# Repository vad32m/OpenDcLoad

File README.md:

#### Configurable parameters

| Configurable parameter | Range        | Granularity | Number of Values |
| ---------------------- | ------------ | ----------- | ---------------- |
| Current (CC mode)      | 0 - 10 A     | 10 mA       | 1000             |
| Voltage (CV mode)      | 1 - 10 V     | 10 mV       | 900              |
|                        | 10 - 100 V   | 100 mV      | 900              |
|                        | 100 - 360 V  | 1 V         | 260              |
| Resistance (CR mode)   | 0.5 - 10 Ohm | 50 mOhm     | 190              |
|                        | 10 - 200 Ohm | 500 mOhm    | 190              |
| Power (CP mode)        | ????         | ????        | ????             |

#### Limits

| Limit type | Applicable mode | Limit value |
| ---------- | --------------- | ----------- |
| Power      | All modes       | 100 W max   |
| Current    | All modes       | 10 A max    |
| Voltage    | All modes       | 1 - 360 V   |
| Resistance | All modes       | 0.5 Ohm min |

#### Measured values

| Measured parameter | Range      | Precision | Number of Values |
| ------------------ | ---------- | --------- | ---------------- |
| Current            | 0 - 1 A    | 1 mA      | 1000             |
|                    | 1 - 10 A   | 10 mA     | 900              |
| Voltage            | 1 - 10 V   | 10 mV     | 900              |
|                    | 10 - 360 V | 100 mV    | 3500             |

#### Parts

Power transistor - IRFP350

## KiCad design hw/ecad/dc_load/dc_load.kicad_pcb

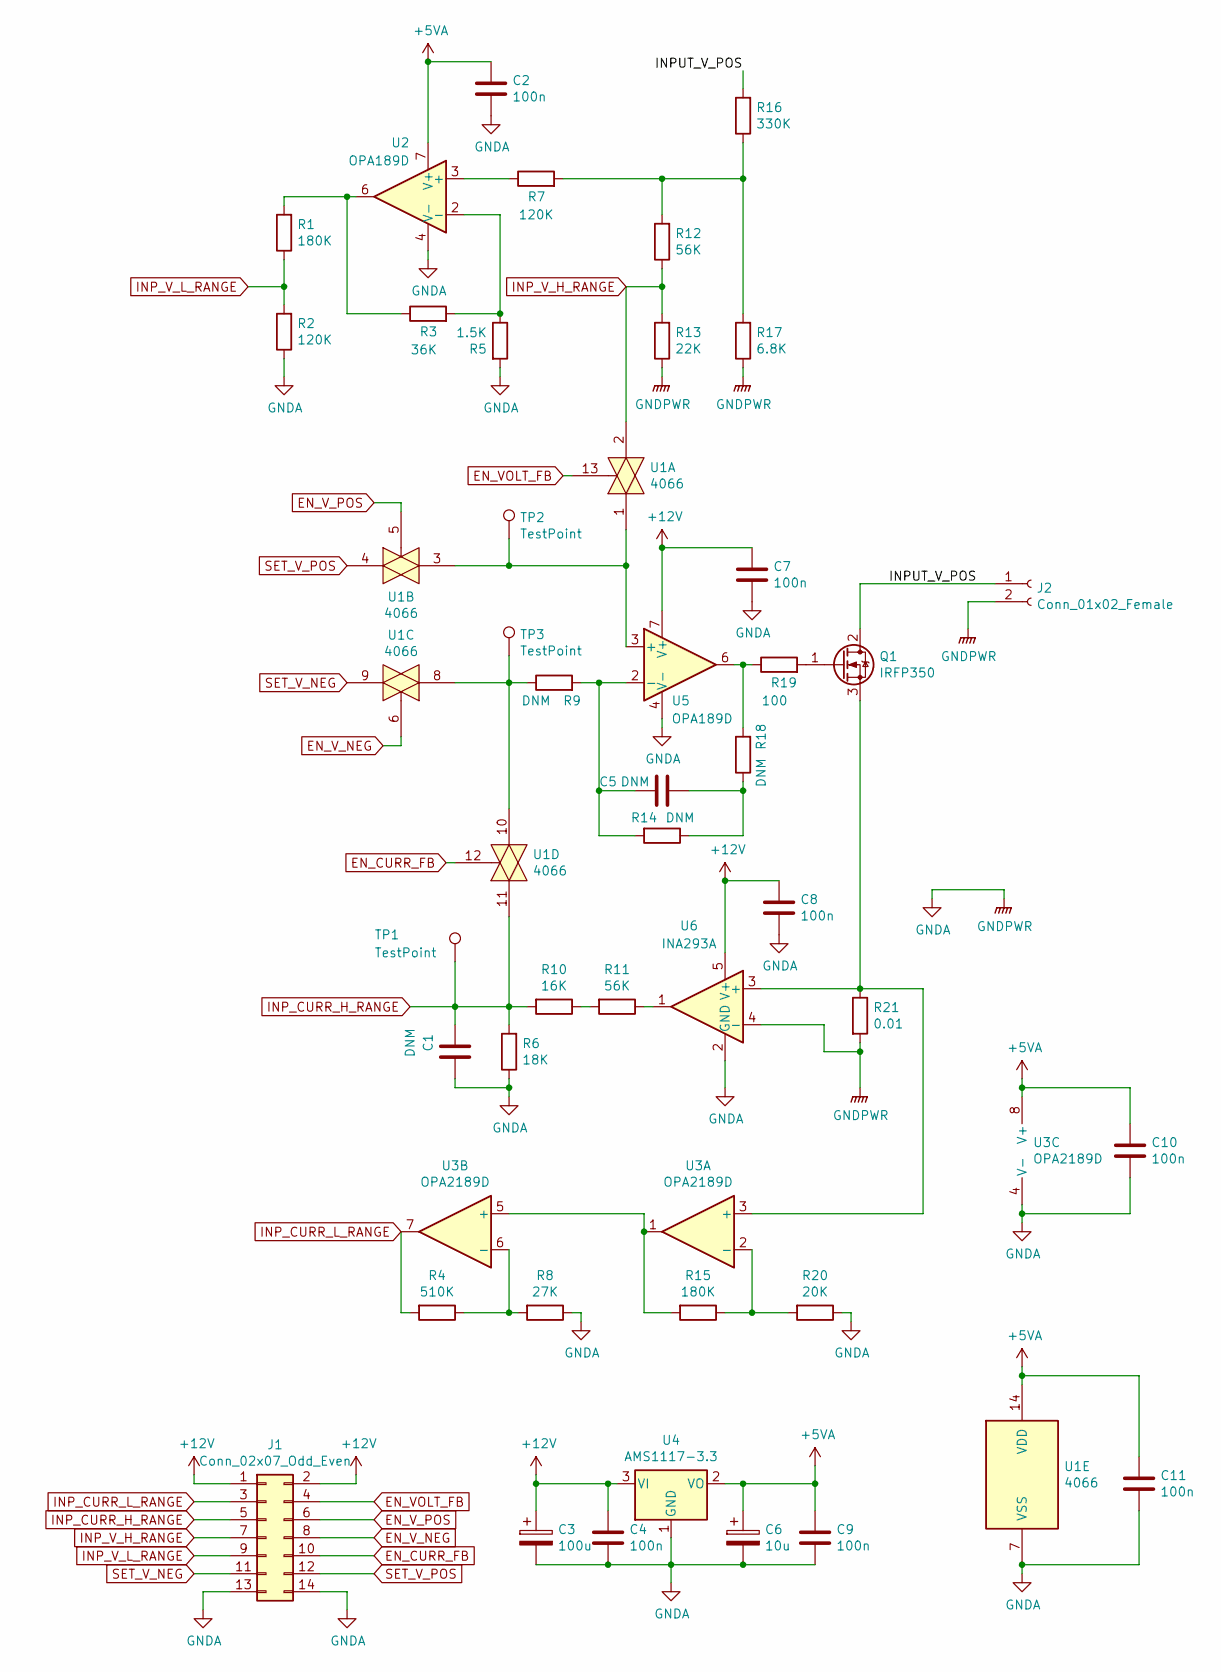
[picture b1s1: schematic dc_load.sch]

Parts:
C1, C5: DNM; C_0805_2012Metric_Pad1.15x1.40mm_HandSolder
C2, C4, C7, C8, C9, C10, C11: 100n; C_0805_2012Metric_Pad1.15x1.40mm_HandSolder
C3: 100u; CP_Radial_D7.5mm_P2.50mm
C6: 10u; CP_Radial_D5.0mm_P2.00mm
J1: Conn_02x07_Odd_Even; IDC-Header_2x07_P2.54mm_Vertical
J2: Conn_01x02_Female; SolderWirePad_1x02_P5.08mm_Drill1.5mm
Q1: IRFP350; TO-247-3_Horizontal_TabDown
R1, R15: 180K; R_0805_2012Metric_Pad1.15x1.40mm_HandSolder
R2, R7: 120K; R_0805_2012Metric_Pad1.15x1.40mm_HandSolder
R3: 36K; R_0805_2012Metric_Pad1.15x1.40mm_HandSolder
R4: 510K; R_0805_2012Metric_Pad1.15x1.40mm_HandSolder
R5: 1.5K; R_0805_2012Metric_Pad1.15x1.40mm_HandSolder
R6: 18K; R_0805_2012Metric_Pad1.15x1.40mm_HandSolder
R8: 27K; R_0805_2012Metric_Pad1.15x1.40mm_HandSolder
R9, R14, R18: DNM; R_0805_2012Metric_Pad1.15x1.40mm_HandSolder
R10: 16K; R_0805_2012Metric_Pad1.15x1.40mm_HandSolder
R11, R12: 56K; R_0805_2012Metric_Pad1.15x1.40mm_HandSolder
R13: 22K; R_0805_2012Metric_Pad1.15x1.40mm_HandSolder
R16: 330K; R_0805_2012Metric_Pad1.15x1.40mm_HandSolder
R17: 6.8K; R_0805_2012Metric_Pad1.15x1.40mm_HandSolder
R19: 100; R_0805_2012Metric_Pad1.15x1.40mm_HandSolder
R20: 20K; R_0805_2012Metric_Pad1.15x1.40mm_HandSolder
R21: 0.01; R_4020_10251Metric_Pad1.65x5.30mm_HandSolder
TP1, TP2, TP3: TestPoint; TestPoint_Pad_D1.5mm
U1: 4066; SOIC-14_3.9x8.7mm_P1.27mm
U2, U5: OPA189D; SOIC-8_3.9x4.9mm_P1.27mm
U3: OPA2189D; SOIC-8_3.9x4.9mm_P1.27mm
U4: AMS1117-3.3; SOT-223-3_TabPin2
U6: INA293A; SOT-23-5

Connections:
+5VA: C2.1, C6.1, C9.1, C10.1, C11.1, U1.14 (VDD), U2.7 (V+), U3.8 (V+), U4.2 (VO)
+12V: C3.1, C4.1, C7.1, C8.1, J1.1, J1.2, U4.3 (VI), U5.7 (V+), U6.5 (V+)
/INPUT_V_POS: J2.1, Q1.2 (D), R16.2
EN_CURR_FB: J1.10, U1.12
EN_VOLT_FB: J1.4, U1.13
EN_V_NEG: J1.8, U1.6
EN_V_POS: J1.6, U1.5
GNDA: C1.2, C2.2, C3.2, C4.2, C6.2, C7.2, C8.2, C9.2, C10.2, C11.2, J1.13, J1.14, J2.2, R2.1, R5.2, R6.1, R8.1, R13.1, R17.1, R20.1, R21.2, U1.7 (VSS), U2.4 (V-), U3.4 (V-), U4.1 (GND), U5.4 (V-), U6.2 (GND), U6.4 (-)
INP_CURR_H_RANGE: C1.1, J1.5, R6.2, R10.2, TP1.1, U1.11
INP_CURR_L_RANGE: J1.3, R4.2, U3.7
INP_V_H_RANGE: J1.7, R12.1, R13.2, U1.2
INP_V_L_RANGE: J1.9, R1.1, R2.2
unnamed: C5.1, R9.2, R14.2, U5.2 (-)
unnamed: C5.2, R14.1, R18.1
unnamed: Q1.1 (G), R19.2
unnamed: Q1.3 (S), R21.1, U3.3 (+), U6.3 (+)
unnamed: R1.2, R3.1, U2.6
unnamed: R3.2, R5.1, U2.2 (-)
unnamed: R4.1, R8.2, U3.6 (-)
unnamed: R7.1, U2.3 (+)
unnamed: R9.1, TP3.1, U1.8, U1.10
unnamed: R10.1, R11.2
unnamed: R11.1, U6.1
unnamed: R7.2, R12.2, R16.1, R17.2
unnamed: R15.1, R20.2, U3.2 (-)
unnamed: R15.2, U3.1, U3.5 (+)
unnamed: R18.2, R19.1, U5.6
unnamed: TP2.1, U1.1, U1.3, U5.3 (+)
SET_V_NEG: J1.11, U1.9
SET_V_POS: J1.12, U1.4

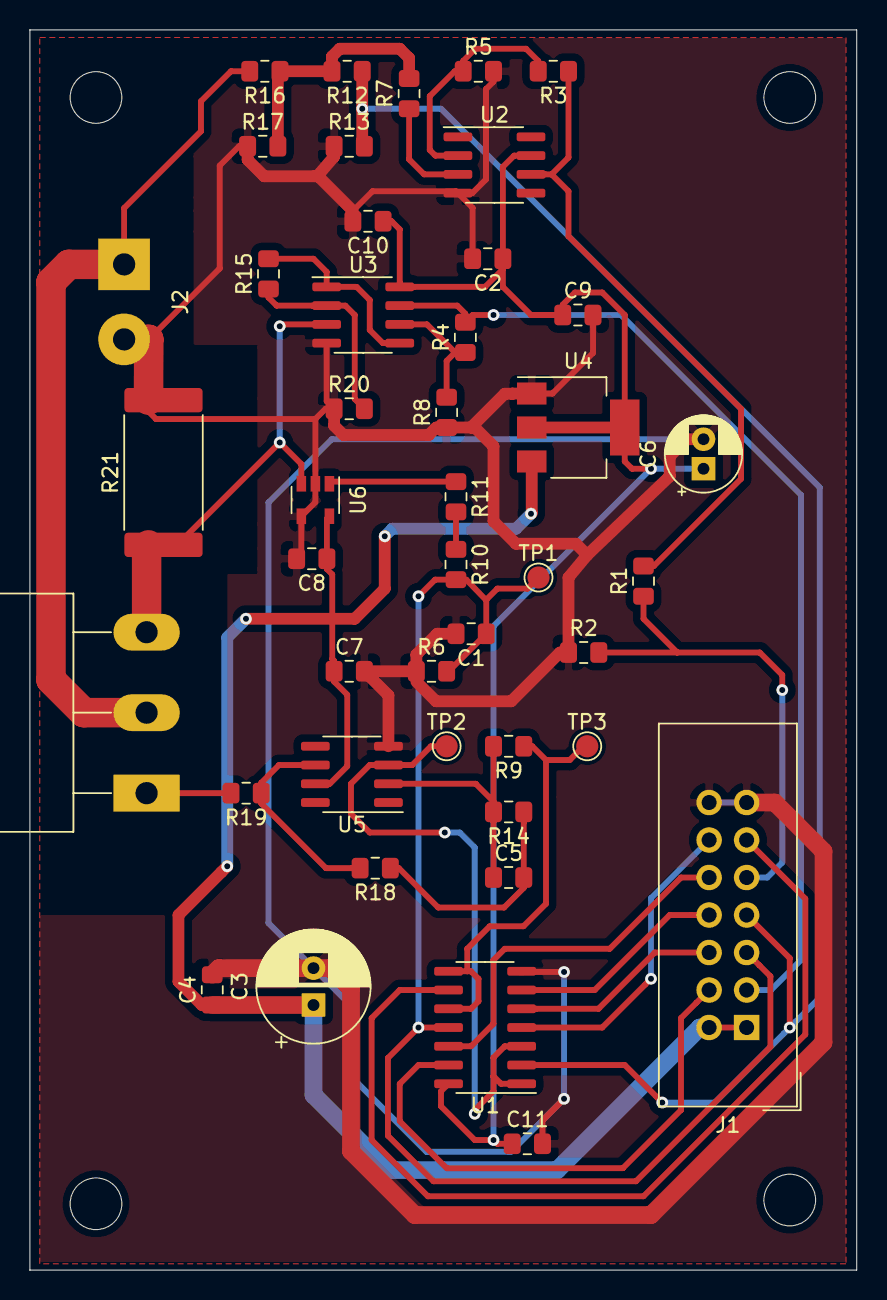
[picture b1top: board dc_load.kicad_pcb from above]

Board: 2 copper layers, 56.0 x 84.0 mm, 44 parts (0 on the bottom side), 30 nets.

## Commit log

2019-02-16 Project setup: initial commit with blinky for libopencm3
2019-02-16 Project setup: add gitignore file
2019-02-16 Project setup: setup makefile-based FreeRTOS build system
2019-03-05 Project setup: makefile based blinky
2019-03-09 Project setup: configure SWV pin and add SWO printf
2019-03-09 Project setup: make separate goals for release and debug builds
2019-04-07 project setup: configure fault handlers and MPU
2019-04-14 project setup: integrate fault handlers submodule
2019-04-14 project setup: fix library inclusion linker flags
2019-04-16 project setup: move from freertos heap implementation to newlib heap
2019-04-16 project setup: add minimal stubs for syscalls
2019-04-21 project setup: update fault handling
2019-04-22 project setup: restore C99 compability
2019-04-23 project setup: move syscalls implementation to platform folder
2019-04-23 project setup: move fault interrupts to separate file
2019-05-05 project setup: update fault handlers submodule, add config for it.
2019-05-05 project setup: update documentation for syscalls header file
2019-05-05 project setup: update fault handlers submodule
2019-05-05 project setup: move core peripheral setup to separate file
2019-05-05 project setup: move the most essential config variables to separate file
2019-05-05 project setup: configure interrupts priority
2019-05-05 project setup: remove unnecessary MPU region
2019-05-08 debug subsystem: add skeleton for logging facility
2019-05-08 debug subsystem: initial implementation for logger API
2019-05-14 debug subsystem: implement async output
2019-05-14 debug subsystem: fix potential buffer overflows in logger
2019-05-15 debug subsystem: add interrupt configuration for logger
2019-05-26 debug subsystem: add macro for run-time assertions
2019-06-24 periph config: add basic config for lcd connection peripherals
2019-07-04 periph config: naming improvements for display connection
2019-07-04 lcd driver: add initial version of the display driver
2019-07-08 periph config: utilize DMA for bulk data transfer on display connection
2019-07-08 lcd driver: use optimized function for display fill
2019-07-14 lcd driver: fix magic numbers and orientation flags
2019-07-14 display connection: add check to preserve DMA transactions overlap
2019-07-14 ldc driver: forward callbacks on bulk data transfers completed
2019-07-14 ui: add littlevgl as a submodule
2019-07-18 ui: add littlevgl demo
2019-07-18 ui: add wireframes for basic work modes
2019-07-18 system config: add assertion to check when we are out of dynamic memory
2019-08-04 architectural design: draft architecture uml diagram
2019-08-04 display to lvgl glue: move to separate file
2019-08-10 ui: add demo screen with plot view
2019-08-10 lvgl lib: replace path to original littlevgl with path to fork
2019-09-22 ui: update lvgl submodule and add example with secondary Y-axis
2019-12-04 ui: add interface and hierarchy skeleton for UI views
2019-12-04 ui: update lvgl submodule to v6.1
2019-12-04 ui: basic implementation for values view
2019-12-04 ui: basic implemetation for plot view
2019-12-07 ui: implementation of parameter setup view
2019-12-08 ui: implementation for mode select view
2019-12-08 ui: add files with layout and replace magic numbers with constants
2019-12-10 platform: add error codes with description
2019-12-10 debug subsystem: add assertion for checking whether current expression is NULL
2019-12-10 ui: add assertions and error codes to views
2019-12-10 makefile: add UI view sources to makefile
2019-12-10 ui: rework mechanism of view activation, improve buttons control
2019-12-11 ui: move basic view header to corresponding directory
2019-12-15 ui: add documentation for the components of user interaction part
2019-12-15 ui: add skeleton for UI components
2019-12-15 ui: draft implementation of the UI architecture
2019-12-15 ftont_panel_controls: initial implemetation of the buttons and encoder driver
2019-12-15 ui: basic implementation of UI controllers with dummy code to demonstrate UI possibilities
2019-12-15 main: remove unused code, add UI initialization
2019-12-23 project core: update fault handlers submodule
2019-12-29 ui: move number invariant out of plot view, so it can be reused
2019-12-29 ui: remove demo code from screen controller
2019-12-29 app logic: add work mode interfaces skeleton
2019-12-30 app logic: add dummy implementation for basic work modes
2019-12-30 ui: make mode select controller build list of available modes
2020-02-10 hardware: add basic analog simulations
2020-03-04 add README.md with parameter description
2020-03-04 hardware: add circuit that combines CV, CC and CR mode frontend
2020-03-15 hardware: add more precise voltage divider for sensing input voltage
2020-03-15 hardware: add ecad project: schematic and PCB
